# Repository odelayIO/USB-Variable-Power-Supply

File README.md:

##### View on [gh-page](https://odelayio.github.io/USB-Variable-Power-Supply/)

# USB Variable Power Supply based on the LM317 Device

## Board Features:

- Variable Output Power between 1.8V to 5V
-	VCC Set by Resistors (0805 Package)
- LED for VCC and +5V Power Rail
-	Header Pin for +5V Output 

<br>
<br>

<br>
<br>
   
<br>
<br>

## Parts List

| Part               | Part Number              | Unit Price | Notes         | Link                                                                                                                         |
|--------------------|--------------------      |------------|---------------|------------------------------------------------------------------------------------------------------------------------------|
| USB Mini Connector | 151-1206-1-ND            | $6.55      | 10 Connectors | http://www.digikey.com/product-detail/en/edac-inc/690-005-299-043/151-1206-1-ND/4312192                                      |
| LM317              | 768-1008-1-ND            | $0.77      | In stock      | http://www.digikey.com/product-detail/en/texas-instruments/LM317DCYR/296-12602-1-ND/443738                                   |
| 0.1uF, 0402, Cap   | 490-6328-1-ND            | $0.55      | 100 capacitor | http://www.digikey.com/product-detail/en/murata-electronics-north-america/GRM155R71C104KA88J/490-6328-1-ND/3845525           |
| 10uF, 0805, Cap    | 1276-6456-1-ND           | $0.78      | 10 capacitor  | http://www.digikey.com/product-detail/en/samsung-electro-mechanics-america-inc/CL21A106KPFNNNG/1276-6456-1-ND/5958084        |
| 143 ohm, 0402      | YAG2980CT-ND             | $0.48      | 100 resistors | http://www.digikey.com/product-detail/en/yageo/RC0402FR-07143RL/YAG2980CT-ND/5281845                                         |
| 240 ohm, 0402      | RMCF0805JT240RCT-ND      | $0.67      | 100 resistors | http://www.digikey.com/product-detail/en/stackpole-electronics-inc/RMCF0805JT240R/RMCF0805JT240RCT-ND/1942545                |
| 392 ohm, 0402      | 311-392CRCT-ND           | $0.87      | 100 resistors | http://www.digikey.com/product-detail/en/yageo/RC0805FR-07392RL/311-392CRCT-ND/730851                                        |
| 1uF, 0402 Cap      | 490-1320-1-ND            | $0.96      | 100 capacitor | http://www.digikey.com/product-detail/en/murata-electronics-north-america/GRM155R60J105KE19D/490-1320-1-ND/587919            |
| Red LED            | SML-D12V1WT86CT-ND       | $1.71      | 10 LEDs       | http://www.digikey.com/product-detail/en/rohm-semiconductor/SML-D12V1WT86/SML-D12V1WT86CT-ND/5843857                         |
| Yellow/Green LED   | SML-D12M1WT86CT-ND       | $1.71      | 10 LEDs       | http://www.digikey.com/product-detail/en/rohm-semiconductor/SML-D12M1WT86/SML-D12M1WT86CT-ND/5843861                         |
| PCB Fab            | 2 layer prototype        | $5.00      | 3 copies      | http://docs.oshpark.com/services/two-layer/                                                                                  |
|                    |                          |            |               |                                                                                                                              |

<br>
<br>

## Additional Information:
- Fab board at [https://oshpark.com/](https://oshpark.com/)
  - Gerber Zip Package was used to fab board

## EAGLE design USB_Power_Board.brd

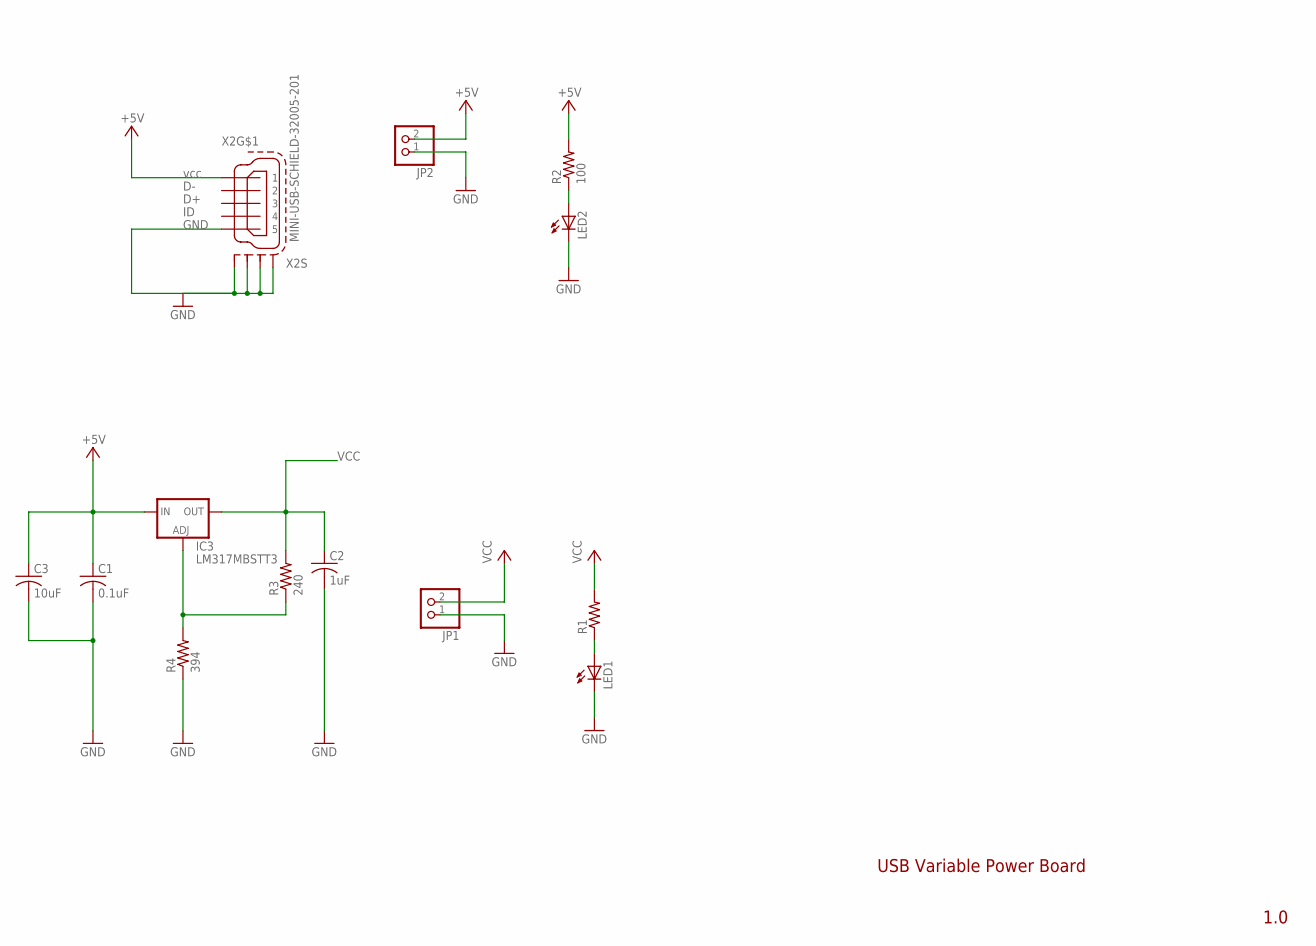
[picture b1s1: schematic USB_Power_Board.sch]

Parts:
C1: 0.1uF; C0402
C2: 1uF; C0402
C3: 10uF; C0603
IC3: LM317MBSTT3; SOT223
JP1, JP2: PINHD-1X2; 1X02
LED1, LED2: LEDCHIP-LED0603; CHIP-LED0603
R1: R-US_R0402; R0402
R2: 100; R0402
R3: 240; R0805
R4: 394; R0805
X2: MINI-USB-SCHIELD-32005-201; 32005-201

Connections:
+5V: C1.1, C3.1, IC3.3 (IN), JP2.2, R2.2, X2.1
GND: C1.2, C2.2, C3.2, JP1.1, JP2.1, LED1.C, LED2.C, R4.1, X2.5, X2.M1 (S1), X2.M2 (S2), X2.M3 (S3), X2.M4 (S4)
unnamed: LED1.A, R1.1
unnamed: IC3.1 (ADJ), R3.1, R4.2
unnamed: LED2.A, R2.1
VCC: C2.1, IC3.4 (OUT), JP1.2, R1.2, R3.2

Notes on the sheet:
USB Variable Power Board
1.0

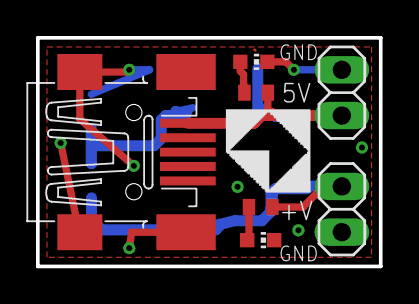
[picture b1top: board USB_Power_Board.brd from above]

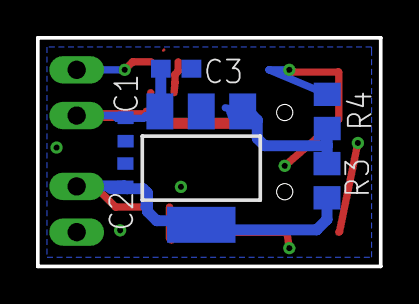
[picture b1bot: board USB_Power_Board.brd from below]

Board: 2 copper layers, 19.1 x 12.7 mm, 13 parts (6 on the bottom side), 6 nets.

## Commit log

2016-10-27 Adding Project Source Files
2016-10-27 Create gh-pages branch via GitHub
2022-12-16 Updated syntax errors
    Added a return char after the "<br>" so the image will load. If two return chars isn't after "<br>", then the image doesn't appear.
